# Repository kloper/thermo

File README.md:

# Thermo

Thermo is a work in progress project aiming to create an electronic thermometer
based on STM32F030 chip.

Follow me on http://kloper.blogspot.com for more info.

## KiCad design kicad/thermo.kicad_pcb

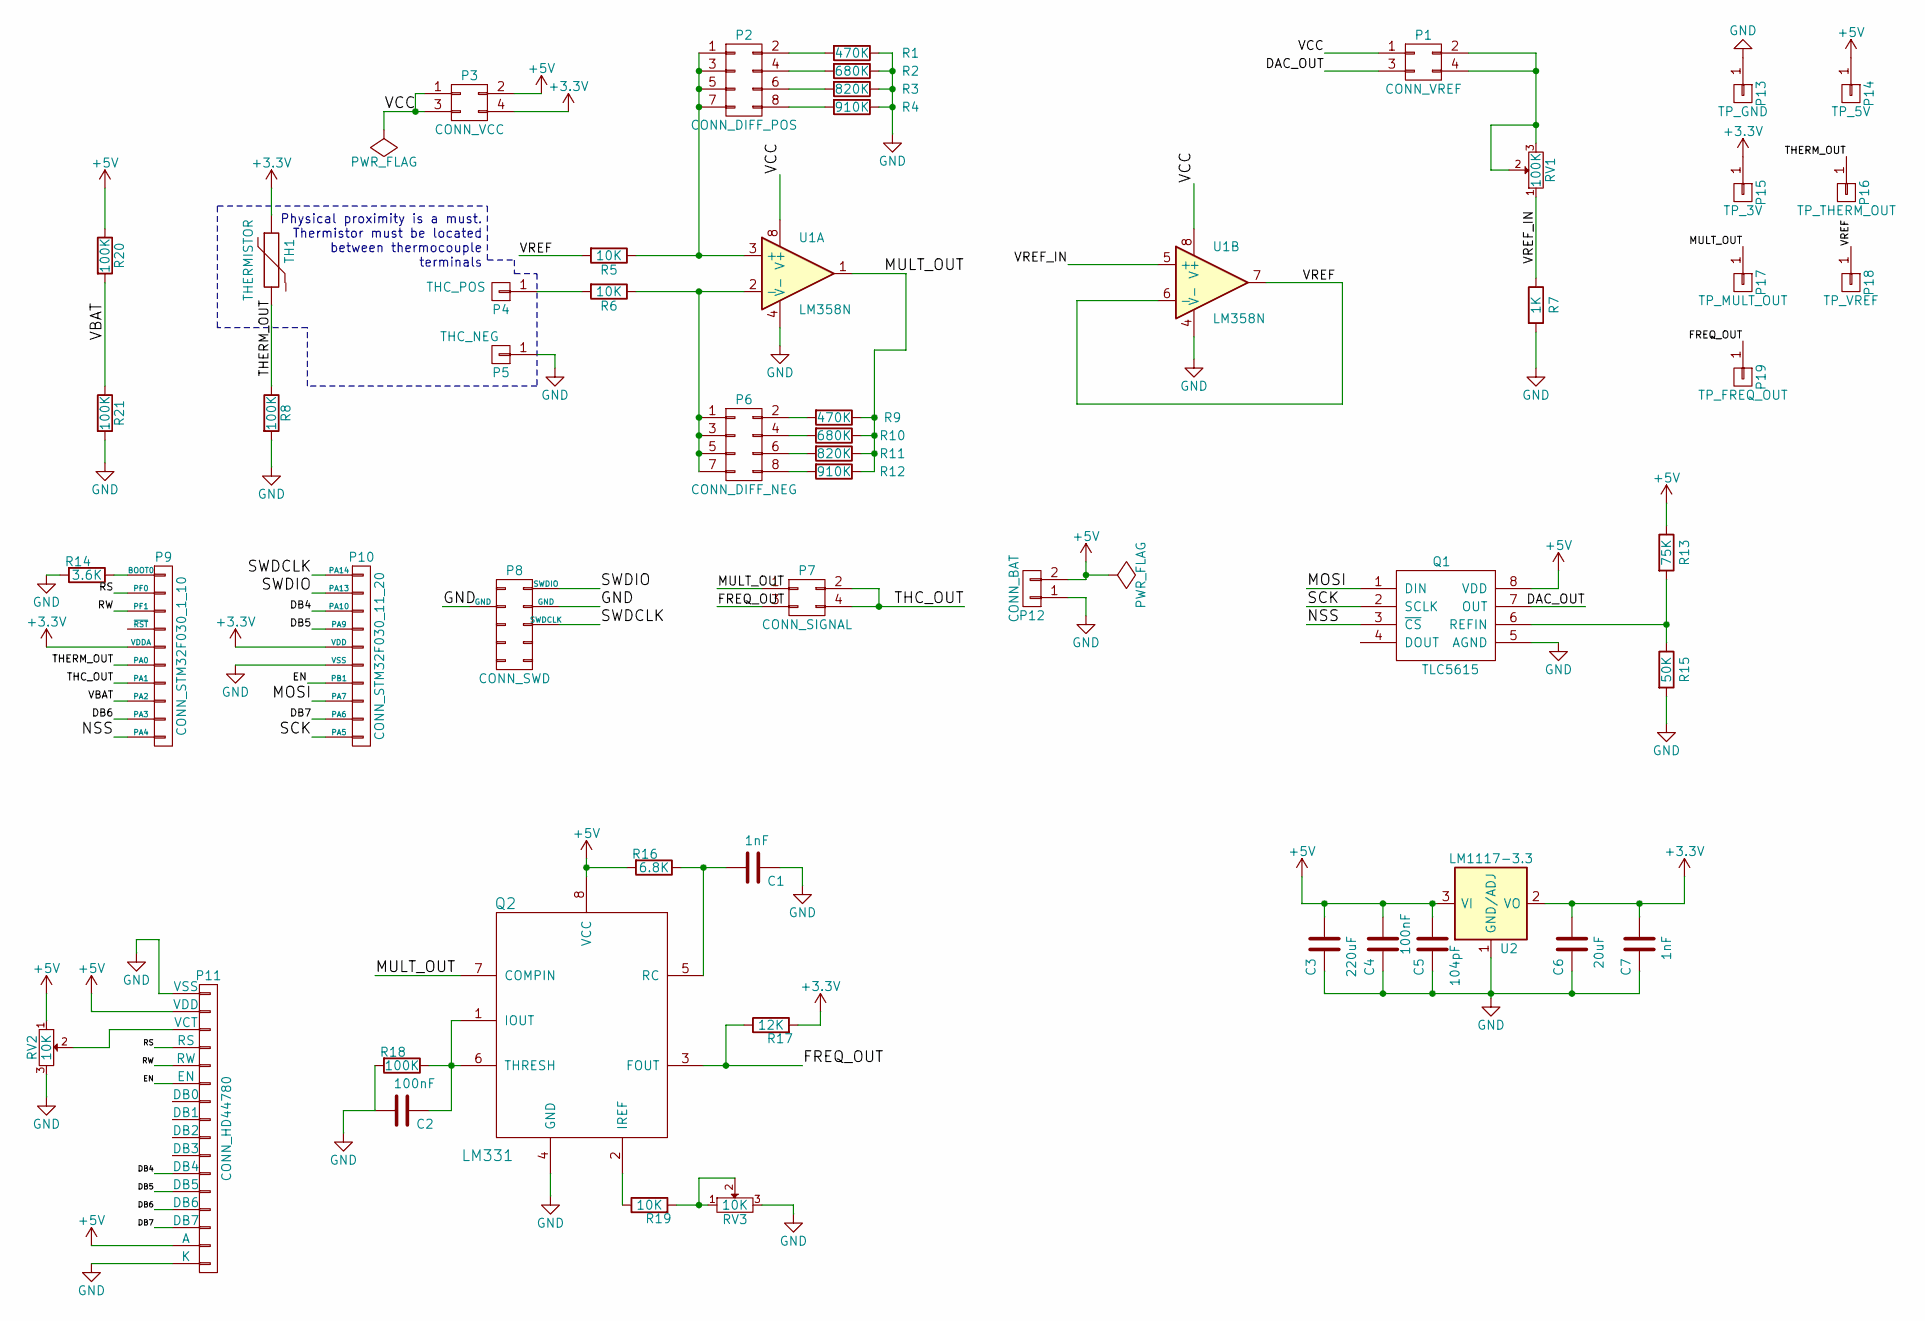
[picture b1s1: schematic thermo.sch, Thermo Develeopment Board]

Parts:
C1, C7: 1nF; C_Rect_L4_W2.5_P2.5
C2, C4: 100nF; C_Rect_L13_W4_P10
C3: 220uF; C_Radial_D5_L6_P2.5
C5: 104pF; C_Rect_L7_W2_P5
C6: 20uF; C_Radial_D5_L6_P2.5
P1: CONN_VREF; Pin_Header_Straight_2x02
P2: CONN_DIFF_POS; Pin_Header_Straight_2x04
P3: CONN_VCC; Pin_Header_Straight_2x02
P4: THC_POS; SolderWirePad_single_2-5mmDrill
P5: THC_NEG; SolderWirePad_single_2-5mmDrill
P6: CONN_DIFF_NEG; Pin_Header_Straight_2x04
P7: CONN_SIGNAL; Pin_Header_Straight_2x02
P8: CONN_SWD; Pin_Header_Straight_2x05
P9: CONN_STM32F030_1_10; Socket_Strip_Straight_1x10
P10: CONN_STM32F030_11_20; Socket_Strip_Straight_1x10
P11: CONN_HD44780; Socket_Strip_Straight_1x16
P12: CONN_BAT; Pin_Header_Straight_1x02
P13: TP_GND; Pin_Header_Straight_1x01
P14: TP_5V; Pin_Header_Straight_1x01
P15: TP_3V; Pin_Header_Straight_1x01
P16: TP_THERM_OUT; Pin_Header_Straight_1x01
P17: TP_MULT_OUT; Pin_Header_Straight_1x01
P18: TP_VREF; Pin_Header_Straight_1x01
P19: TP_FREQ_OUT; Pin_Header_Straight_1x01
Q1: TLC5615; DIP-8_W7.62mm
Q2: LM331; DIP-8_W7.62mm
R1, R9: 470K; R_0805_HandSoldering
R2, R10: 680K; R_0805_HandSoldering
R3, R11: 820K; R_0805_HandSoldering
R4, R12: 910K; R_0805_HandSoldering
R5, R6, R19: 10K; R_0805_HandSoldering
R7: 1K; R_0805_HandSoldering
R8, R18, R20, R21: 100K; R_0805_HandSoldering
R13: 75K; R_0805_HandSoldering
R14: 3.6K; R_0805_HandSoldering
R15: 50K; R_0805_HandSoldering
R16: 6.8K; R_0805_HandSoldering
R17: 12K; R_0805_HandSoldering
RV1: 100K; Potentiometer_Bourns_3296W_3-8Zoll_Inline_ScrewUp
RV2, RV3: 10K; Potentiometer_Bourns_3296W_3-8Zoll_Inline_ScrewUp
TH1: THERMISTOR; Resistor_Horizontal_RM12mm
U1: LM358N; DIP-8_W7.62mm
U2: LM1117-3.3; SOT-223

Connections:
+3V3: C6.2, C7.2, P3.4, P9.5 (VDDA), P10.5 (VDD), P15.1, R17.2, TH1.1, U2.2 (VO), U2.4 (VO)
+5V: C3.2, C4.2, C5.2, P3.2, P11.2 (VDD), P11.15 (A), P12.2, P14.1, Q1.8 (VDD), Q2.8 (VCC), R13.1, R16.2, R20.1, RV2.1, U2.3 (VI)
/DAC_OUT: P1.3, Q1.7 (OUT)
/DB4: P10.3 (PA10), P11.11 (DB4)
/DB5: P10.4 (PA9), P11.12 (DB5)
/DB6: P9.9 (PA3), P11.13 (DB6)
/DB7: P10.9 (PA6), P11.14 (DB7)
/EN: P10.7 (PB1), P11.6 (EN)
/FREQ_OUT: P7.3, P19.1, Q2.3 (FOUT), R17.1
/MOSI: P10.8 (PA7), Q1.1 (DIN)
/MULT_OUT: P7.1, P17.1, Q2.7 (COMPIN), R9.1, R10.1, R11.1, R12.1, U1.1
/NSS: P9.10 (PA4), Q1.3 (~CS)
/RS: P9.2 (PF0), P11.4 (RS)
/RW: P9.3 (PF1), P11.5 (RW)
/SCK: P10.10 (PA5), Q1.2 (SCLK)
/SWDCLK: P8.6 (SWDCLK), P10.1 (PA14)
/SWDIO: P8.2 (SWDIO), P10.2 (PA13)
/THC_OUT: P7.2, P7.4, P9.7 (PA1)
/THERM_OUT: P9.6 (PA0), P16.1, R8.1, TH1.2
/VBAT: P9.8 (PA2), R20.2, R21.1
/VCC: P1.1, P3.1, P3.3, U1.8 (V+)
/VREF: P18.1, R5.2, U1.6 (-), U1.7
/VREF_IN: R7.1, RV1.1, U1.5 (+)
GND: C1.1, C2.2, C3.1, C4.1, C5.1, C6.1, C7.1, P5.1, P8.3 (GND), P8.4 (GND), P10.6 (VSS), P11.1 (VSS), P11.16 (K), P12.1, P13.1, Q1.5 (AGND), Q2.4 (GND), R1.1, R2.1, R3.1, R4.1, R7.2, R8.2, R14.2, R15.2, R18.2, R21.2, RV2.3, RV3.3, U1.4 (V-), U2.1 (GND/ADJ)
unnamed: C1.2, Q2.5 (RC), R16.1
unnamed: C2.1, Q2.1 (IOUT), Q2.6 (THRESH), R18.1
unnamed: P1.2, P1.4, RV1.2, RV1.3
unnamed: P2.1, P2.3, P2.5, P2.7, R5.1, U1.3 (+)
unnamed: P2.2, R1.2
unnamed: P2.4, R2.2
unnamed: P2.6, R3.2
unnamed: P2.8, R4.2
unnamed: P4.1, R6.2
unnamed: P6.1, P6.3, P6.5, P6.7, R6.1, U1.2 (-)
unnamed: P6.2, R9.2
unnamed: P6.4, R10.2
unnamed: P6.6, R11.2
unnamed: P6.8, R12.2
unnamed: P9.1 (BOOT0), R14.1
unnamed: P11.3 (VCT), RV2.2
unnamed: Q1.6 (REFIN), R13.2, R15.1
unnamed: Q2.2 (IREF), R19.1
unnamed: R19.2, RV3.1, RV3.2

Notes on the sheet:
Physical proximity is a must. Thermistor must be located between thermocouple terminals

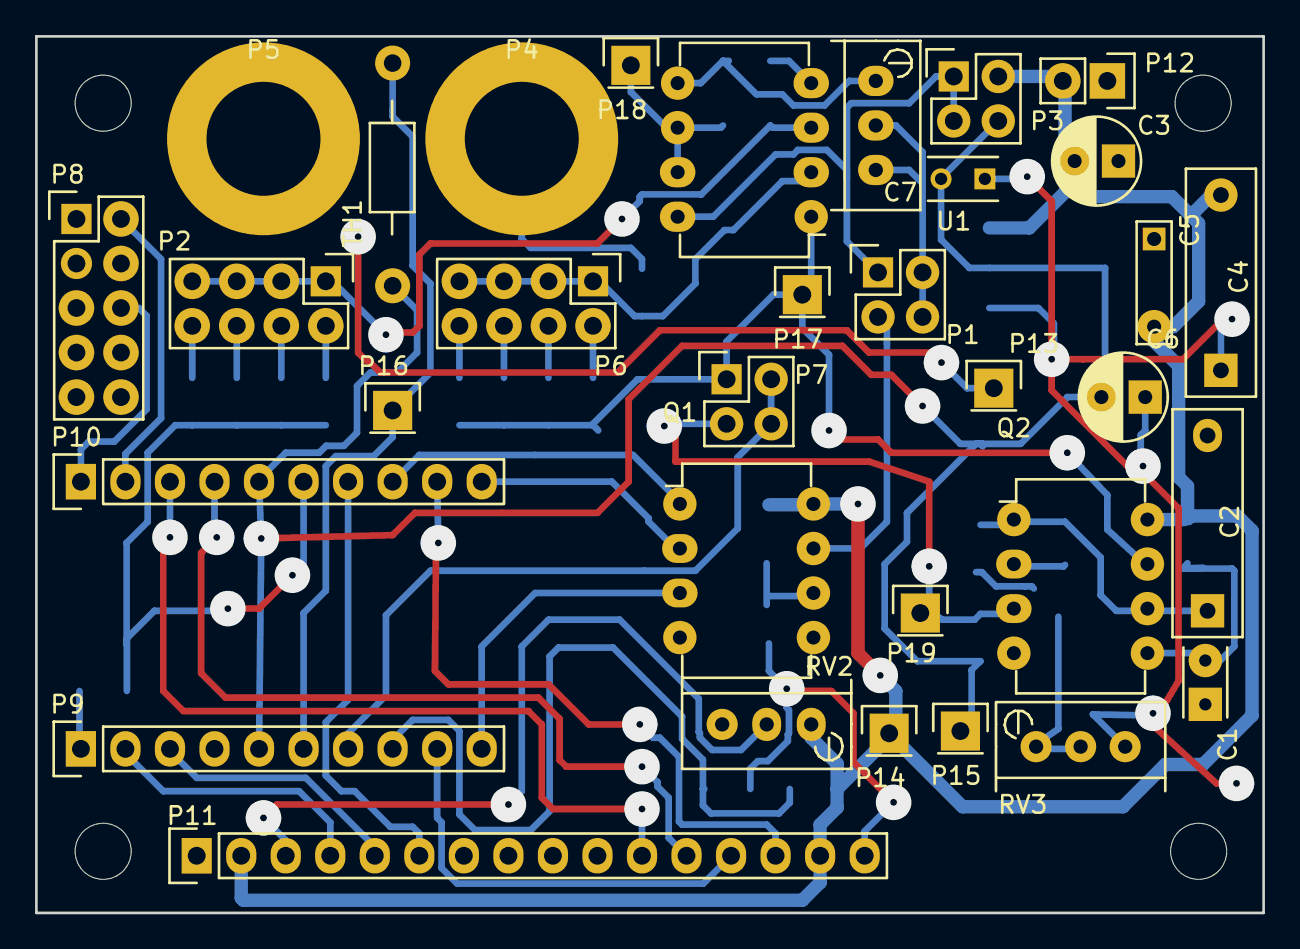
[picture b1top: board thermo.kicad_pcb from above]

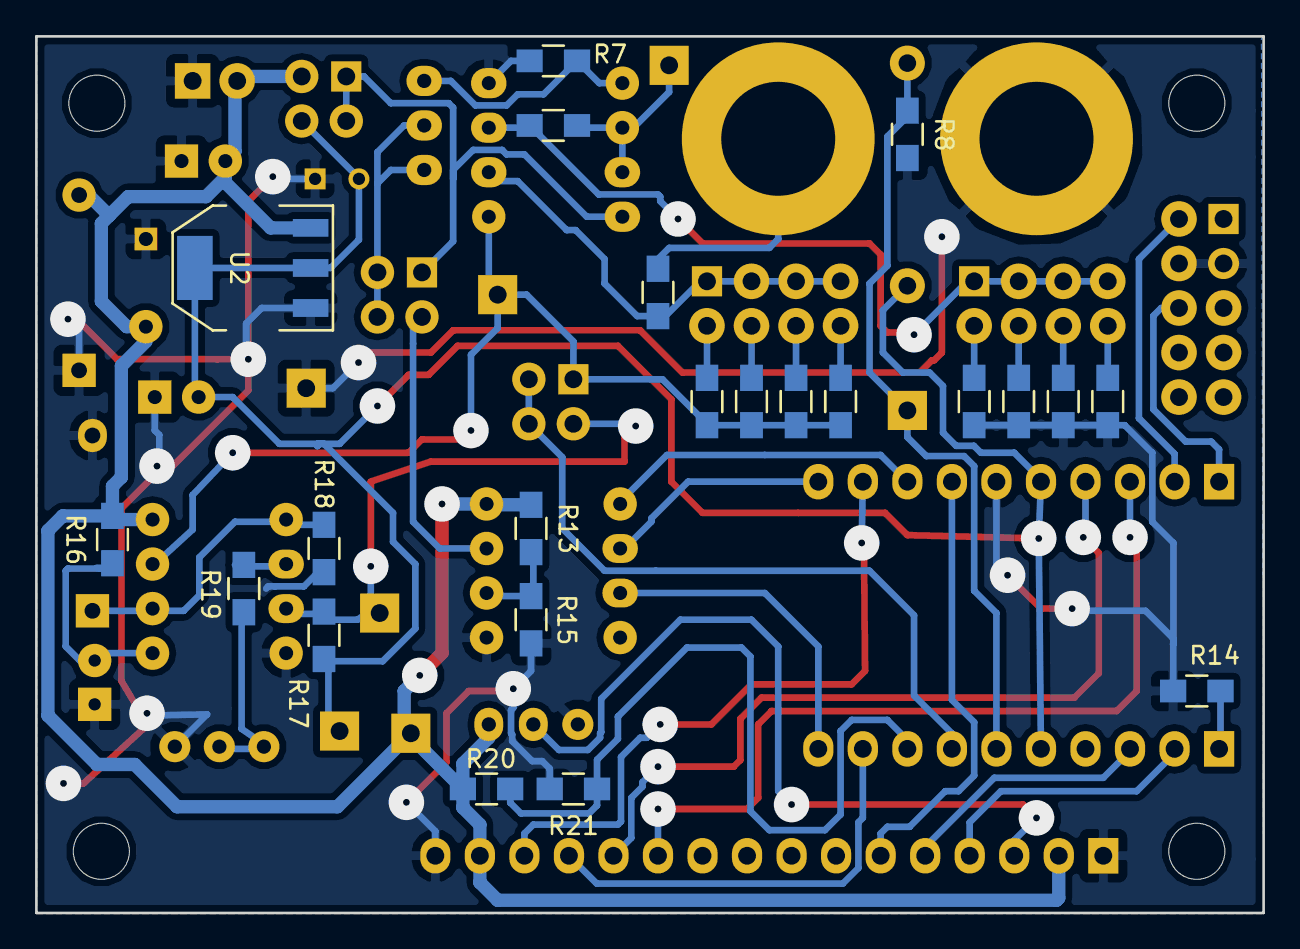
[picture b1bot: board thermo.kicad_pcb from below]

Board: 2 copper layers, 70.0 x 50.0 mm, 55 parts (22 on the bottom side), 43 nets.

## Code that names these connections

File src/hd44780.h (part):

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 * @{
 */

#define HD44780_RS 0U /**< PF0 */
#define HD44780_RW 1U /**< PF1 */
#define HD44780_EN 1U /**< PB1 */
#define HD44780_DB4 10U /**< PA10 */
#define HD44780_DB5 9U /**< PA9 */
#define HD44780_DB6 3U /**< PA3 */
#define HD44780_DB7 6U /**< PA6 */


/** @} */
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
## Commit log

2016-07-20 Initial import of empty sample project
    Auto-generated by eclipse STM32 plug-in
2016-07-23 Add file header templates for emacs
2016-07-23 Introduce .gitignore file
2016-07-23 Introduce a simple HD44780 display driver
    This is a simple and not very efficient port
    of pato HD44780 driver
2016-07-24 Introduce busy waiting based on TIM3
    Created very simple delay mechanism based on TIM3.
    In order to make fixed time delay we run the counter and wait
    for overrun interrupt in kind of busy wait, but with WFI
    which is hopefully less power consuming than simple
    looping.
    HD44780 code now uses the delay in display reset.
2016-07-24 Add images from the blog
2016-07-26 Fix initial counter value in delay
2016-07-26 Introduce basic ADC acquisition
2016-07-30 Introduce Steinhard-Hart temperature approximation
    1. ADC has been switched to run on slowes cycle.
    2. Added reference to VREFINT_CAL and used it to convert ADC values to
    actual voltages.
    3. Added linear approximation for Steinhart-Hart equation to
    transform ADC voltage read from thermistor to a temperature.
    4. Added python code used to calculate the linear approximation.
2016-07-30 Add more stuff to .gitignore
2016-08-12 Add calculation of optimum sense resistor
2016-08-12 Introduce expotential averaging of ADC values
2016-08-12 Introduce delay_1us() delay macro
2016-08-12 Add delays to display functions + rewire display
    Physical connections changed, so the port definitions in the header.
    Added a few more NOPs into nibble_in/out operations to skip display
    artefacts.
2016-08-12 Change Steinhart-Hart lenear approximation...
    ... to match new sense resistor and range.
2016-08-12 Use average values in main, fix formatting bug
2016-08-12 Introduce ipython notebook for blog entry about thermistors
2016-08-12 Add missing thermistor schematics PNG
2016-08-12 Fix binary search upper bound initial value
    The upper index referencing a value beyond array
    causing possible out-of-bounds array access.
2016-08-12 Scale down thermistor schematics image
    Make it inline in the thermistor notebook
2016-08-12 Again, trying to make schematics image to show
2016-08-12 Yet another attempt to fix schematics
2016-08-17 Fix missing plots in thermistor notebook
2016-08-21 Factor out nop delays into a macro
2016-08-21 Factor out binary search and linear approximation into a separate API
2016-08-21 Make ADC to use fixed width average instead of exponential average
    The fixed width average resets after a predefined number of samples.
    It has a potential of spikes but has less 'memory' as the
    exponential average does.
2016-08-21 Make the delay mechanism use processor events
    The problem with using of WFI is rase condition when
    the timer interrupt occurs just between condition check and
    WFI instruction and no additional interrupts
    occur. Then WFI blcoks forever.
2016-08-23 Make intermediate result of linear approximation to be 64-bit
    ... to get more precise result.
2016-08-23 Introduce thermocouple ADC to Celsius conversion
2016-08-23 Display cold and hot junction temperatures
2016-08-25 Fix some type conversion compiler warnings
    Most of the warnings are about constant to value
    conversion which is normally done ok by compiler.
2016-08-25 Fix display noise quirk and remove unneeded delays
    The quirk is caused by not cleaning the data bus lines
    after nibble out operation. This caused the next nibble out
    to latch wring bus value immediately after EN goes high.
2016-08-25 Switch to -O1 compilation optimization
2016-10-12 Temporary disable pull up/downs on HD44780 GPIO lines...
    ... add temporary delays to HD44780.
2016-10-12 Disable IRQs during display handling
2016-10-12 Update ipython notebook for thermocouples
2016-10-12 Add prototype board KiCad project
2016-10-22 Fix Vss and Vdd swapped on display connector
2016-10-25 Make HD44780 with the new dev board
2016-10-25 Dev board has non-optimal 100K resistor in parallel with thermistor...
    Changed thermistor linear approximation to reflect that.
2016-11-19 Automatic update of project settings after migrating to Eclipse Neon
    Author: Dimitry Kloper <kloper@users.sf.com>
2016-11-19 Introduce run-time slow median filter on ADC values
    The filter works by saving 10 average values in FIFO per ADC channel
    and then infrequently applying sort to the queue and getting the
    median value.
    The implementation of the filter is inefficient but since the
    sorting is invoked infrequently I can live with it.
2016-12-10 Adapt code for new dev board settings
    1. The r2 resistors on lm358 has been set to 910K
    2. Vref = 10mV + Voffset

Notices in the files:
src/hd44780.h:
Copyright (c) 2016, Dimitry Kloper.
All rights reserved.
